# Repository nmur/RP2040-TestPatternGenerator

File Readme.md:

# RP2040-TestPatternGenerator

This is a simple test pattern generator that runs on the RP2040 microcontroller. It uses the [PicoVGA cmake](https://github.com/codaris/picovga-cmake) library for outputting a 15kHz 240p RGBS signal via a VGA connector. This tool is aimed to be used for rudimentary tests for checking basic CRT TV functionality, not for accurate calibration.  

Its main features are:  
- **Cheap**: Approximately <$15 USD in parts, less if you already have some components or if you want to make a few.
- **Accessible**: Open source. Soldering is easy enough even for a first timer.
- **Small**: Roughly 2x2"/50x50mm in size.
- **Fast**: Boots and changes patterns instantly.
- **Portable**: Very low power draw, works with a powerbank.

## Limitations

This program can only output colours in the RGB332 space, so each of the three colour channels (Red, Green, and Blue) are represented by 3, 3, and 2 bits, respectively. More information can be found [here](https://github.com/nmur/RP2040-TestPatternGenerator/wiki/Limitations).

## Getting Started

1. [Obtain all the components and assemble the device](https://github.com/nmur/RP2040-TestPatternGenerator/wiki/Assembly).
2. Download the [latest firmware](https://github.com/nmur/RP2040-TestPatternGenerator/releases).
3. Hold the BOOT button on the RP2040 device and connect it to your PC. A file browser window for the device should appear.
4. Drag and drop the `RP2040-TestPatternGenerator.uf2` file onto the device. It should automatically close when completed.

## How to Use

- [Connect the device to your TV](https://github.com/nmur/RP2040-TestPatternGenerator/wiki/Frequently-Asked-Questions#how-do-i-connect-this-to-my-crt-tv), and connect a USB-C cable for power.
- Press the connected button to cycle through patterns.
- To flash a newer firmware, follow the same firmware installation steps from the [Getting Started](https://github.com/nmur/RP2040-TestPatternGenerator/tree/main?tab=readme-ov-file#getting-started) section. Once the device is installed in an enclosure and the BOOT button is inaccessable, connect the device to your computer, hold the same button for 3 seconds and release. The device will reboot into flash mode.

## Building

1. Generate the make files by running CMake:
~~~
cmake .
~~~

2. Build the project:
~~~
make
~~~

## Acknowledgements

- Miroslav Nemecek (Panda38@seznam.cz) for their [PicoVGA library](https://github.com/Panda381/PicoVGA)
- Wayne Venables (codaris) for their [PicoVGA fork](https://github.com/codaris/picovga-cmake)
- Turi Scandurra (TuriSc) for their [RP2040-Button library](https://github.com/TuriSc/RP2040-Button)

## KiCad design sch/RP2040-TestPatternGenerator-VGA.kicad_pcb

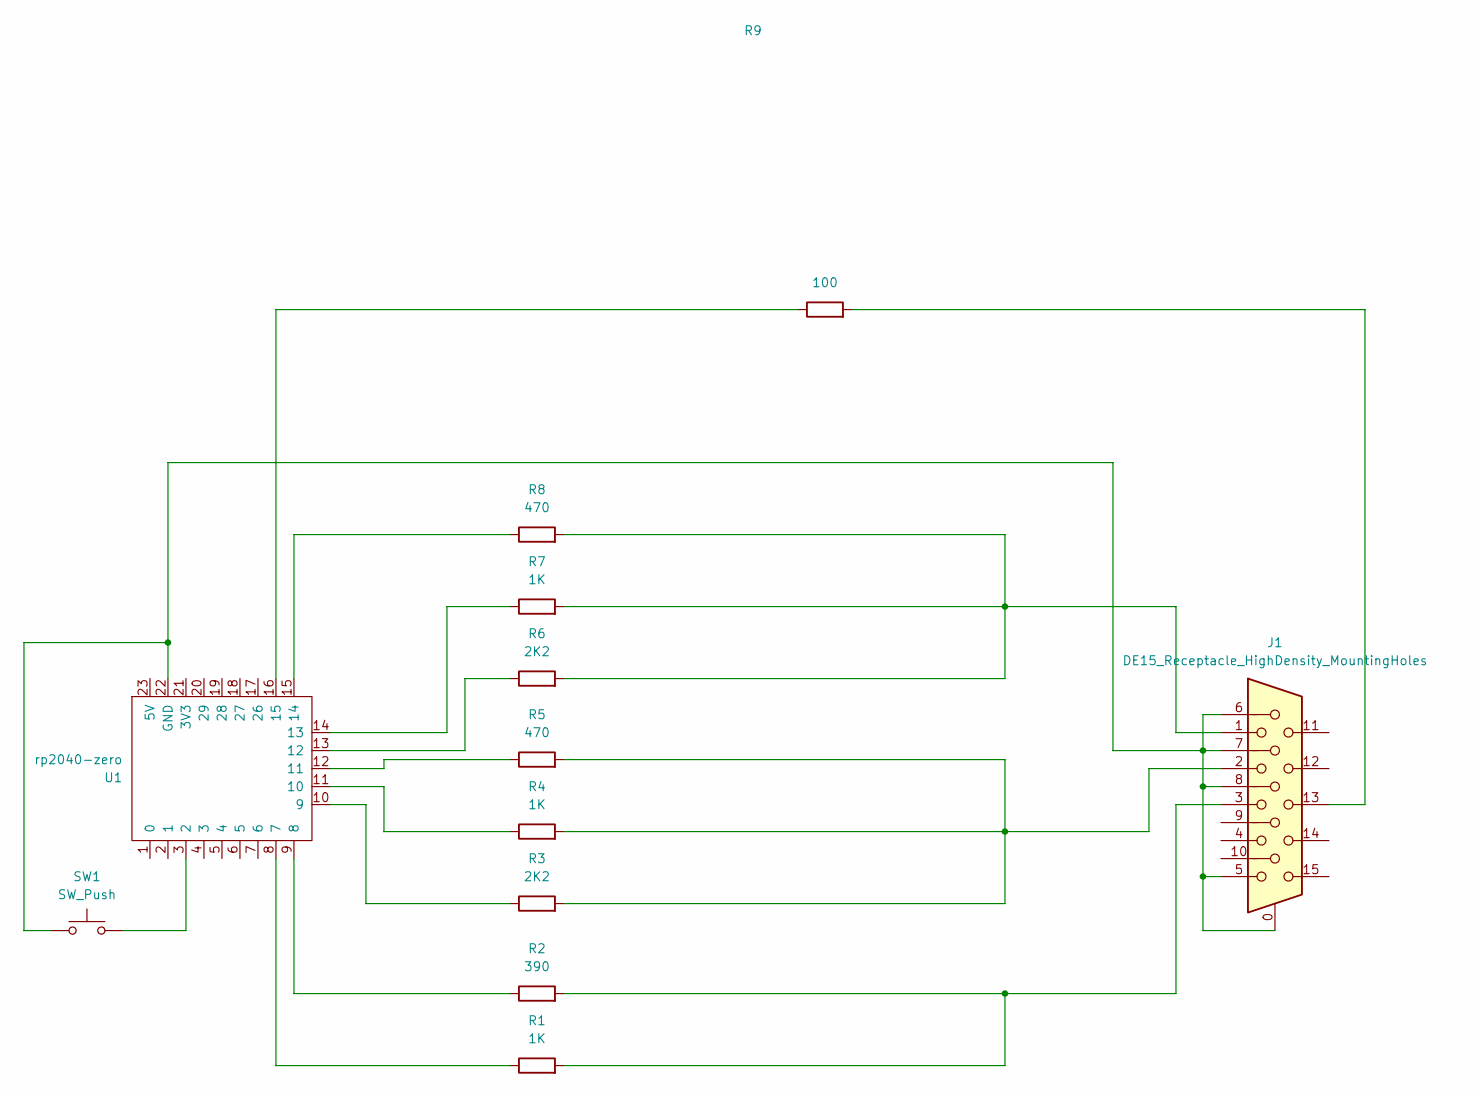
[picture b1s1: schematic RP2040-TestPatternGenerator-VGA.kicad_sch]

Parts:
J1: DE15_Receptacle_HighDensity_MountingHoles; DSUB-15-HD_Female_Horizontal_P2.29x1.98mm_EdgePinOffset3.03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
R1, R4, R7: 1K; R_Axial_DIN0207_L6.3mm_D2.5mm_P10.16mm_Horizontal
R2: 390; R_Axial_DIN0207_L6.3mm_D2.5mm_P10.16mm_Horizontal
R3, R6: 2K2; R_Axial_DIN0207_L6.3mm_D2.5mm_P10.16mm_Horizontal
R5, R8: 470; R_Axial_DIN0207_L6.3mm_D2.5mm_P10.16mm_Horizontal
R9: 100; R_Axial_DIN0207_L6.3mm_D2.5mm_P10.16mm_Horizontal
SW1: SW_Push; SW_Tactile_SPST_Angled_PTS645Vx58-2LFS
U1: rp2040-zero; rp2040-zero-smd

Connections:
unnamed 0: J1.1, R6.2, R7.2, R8.2; also elsewhere on the board
unnamed 1: J1.2, R3.2, R4.2, R5.2; also elsewhere on the board
unnamed 2: J1.3, R1.2, R2.2; also elsewhere on the board
unnamed 3: J1.13, R9.2; also elsewhere on the board
unnamed: SW1.2, U1.3 (2)
unnamed: R1.1, U1.8 (7)
unnamed: R2.1, U1.9 (8)
unnamed: R3.1, U1.10 (9)
unnamed: R4.1, U1.11 (10)
unnamed: R5.1, U1.12 (11)
unnamed: R6.1, U1.13 (12)
unnamed: R7.1, U1.14 (13)
unnamed: R8.1, U1.15 (14)
unnamed: R9.1, U1.16 (15)
unnamed 14: J1.0, J1.5, J1.6, J1.7, J1.8, SW1.1, U1.22 (GND); also elsewhere on the board

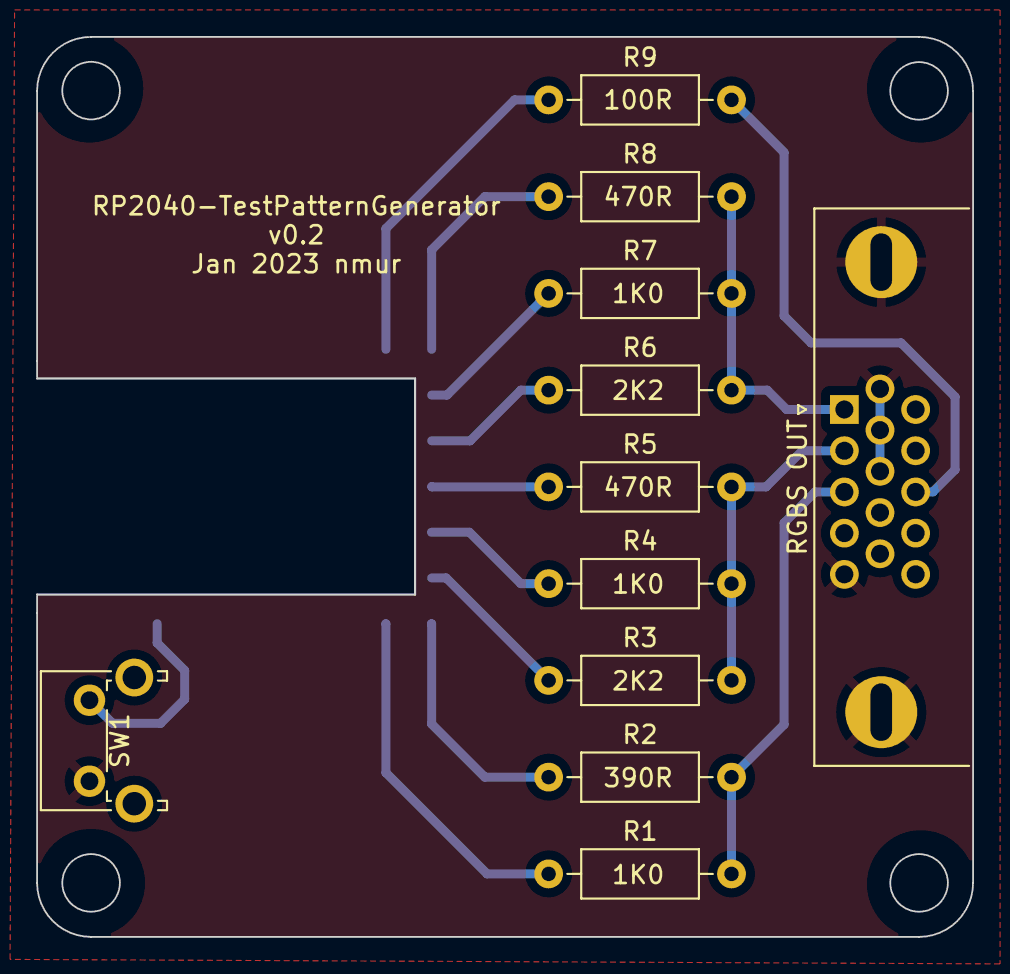
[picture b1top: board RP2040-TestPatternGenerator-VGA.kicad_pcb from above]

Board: 2 copper layers, 52.0 x 50.0 mm, 12 parts (1 on the bottom side), 15 nets.

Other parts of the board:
RGBS OUT: DE15_Receptacle_HighDensity_MountingHoles; DSUB-15-HD_Female_Horizontal_P2.29x1.98mm_EdgePinOffset3.03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

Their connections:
unnamed 0: RGBS OUT.1; also elsewhere on the board
unnamed 1: RGBS OUT.2; also elsewhere on the board
unnamed 2: RGBS OUT.3; also elsewhere on the board
unnamed 3: RGBS OUT.13; also elsewhere on the board
unnamed 14: RGBS OUT.0, RGBS OUT.5, RGBS OUT.6, RGBS OUT.7, RGBS OUT.8; also elsewhere on the board

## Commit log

2024-01-14 copy the contents of the hello-world project as a starting point
2024-01-14 updated the readme
2024-01-14 updated the readme some more
2024-01-14 changed the executable name in the cmake file
2024-01-14 modified hello world text to output 240p
2024-01-14 added monoscope file and attempted display it on screen
2024-01-14 regenerated an uncompressed version of the monoscope pattern file, now works well
2024-01-28 edited pin configuration for optimal layout for Waveshare RP2040-Zero
2024-01-28 added the RP2040-Button library
2024-01-28 added basic button handling (just displays text on screen)
2024-01-28 Create LICENSE
2024-01-28 added grid pattern and code to switch to grid on button press (grid image was converted incorrectly)
2024-01-28 updated readme with RP2040-Button acknowledgements
2024-01-29 added submodules and modified cmake files to use them if they exist
2024-01-29 added v0.1 gerber files (untested IRL)
2024-01-29 created python script which converts a png to an RGB332 hex array
2024-01-29 fixed grid colours
2024-01-29 reworked the included test patterns, and added functionality to cycle through them
2024-01-30 new gerber files for smaller PCB
2024-01-30 added long press handling to reboot into flash mode
2024-01-30 minor refactor
2024-02-08 Added completely white screen
2024-02-08 added png file
2024-02-11 added photos
2024-02-21 added existing VGA PCB/schematic and also a new VGA + Composite video schematic (no PCB yet)
2024-02-23 added library files for schematics and footprints for a successful PCB conversion
2024-02-23 finalised PCB size/holes based on 100x66x38mm enclosure
2024-02-23 actual final dimensions
2024-02-23 finalised PCB size/holes based on 100x60x25mm enclosure
2024-02-26 first attempt at positioning all components before traces
2025-06-12 Create temp
